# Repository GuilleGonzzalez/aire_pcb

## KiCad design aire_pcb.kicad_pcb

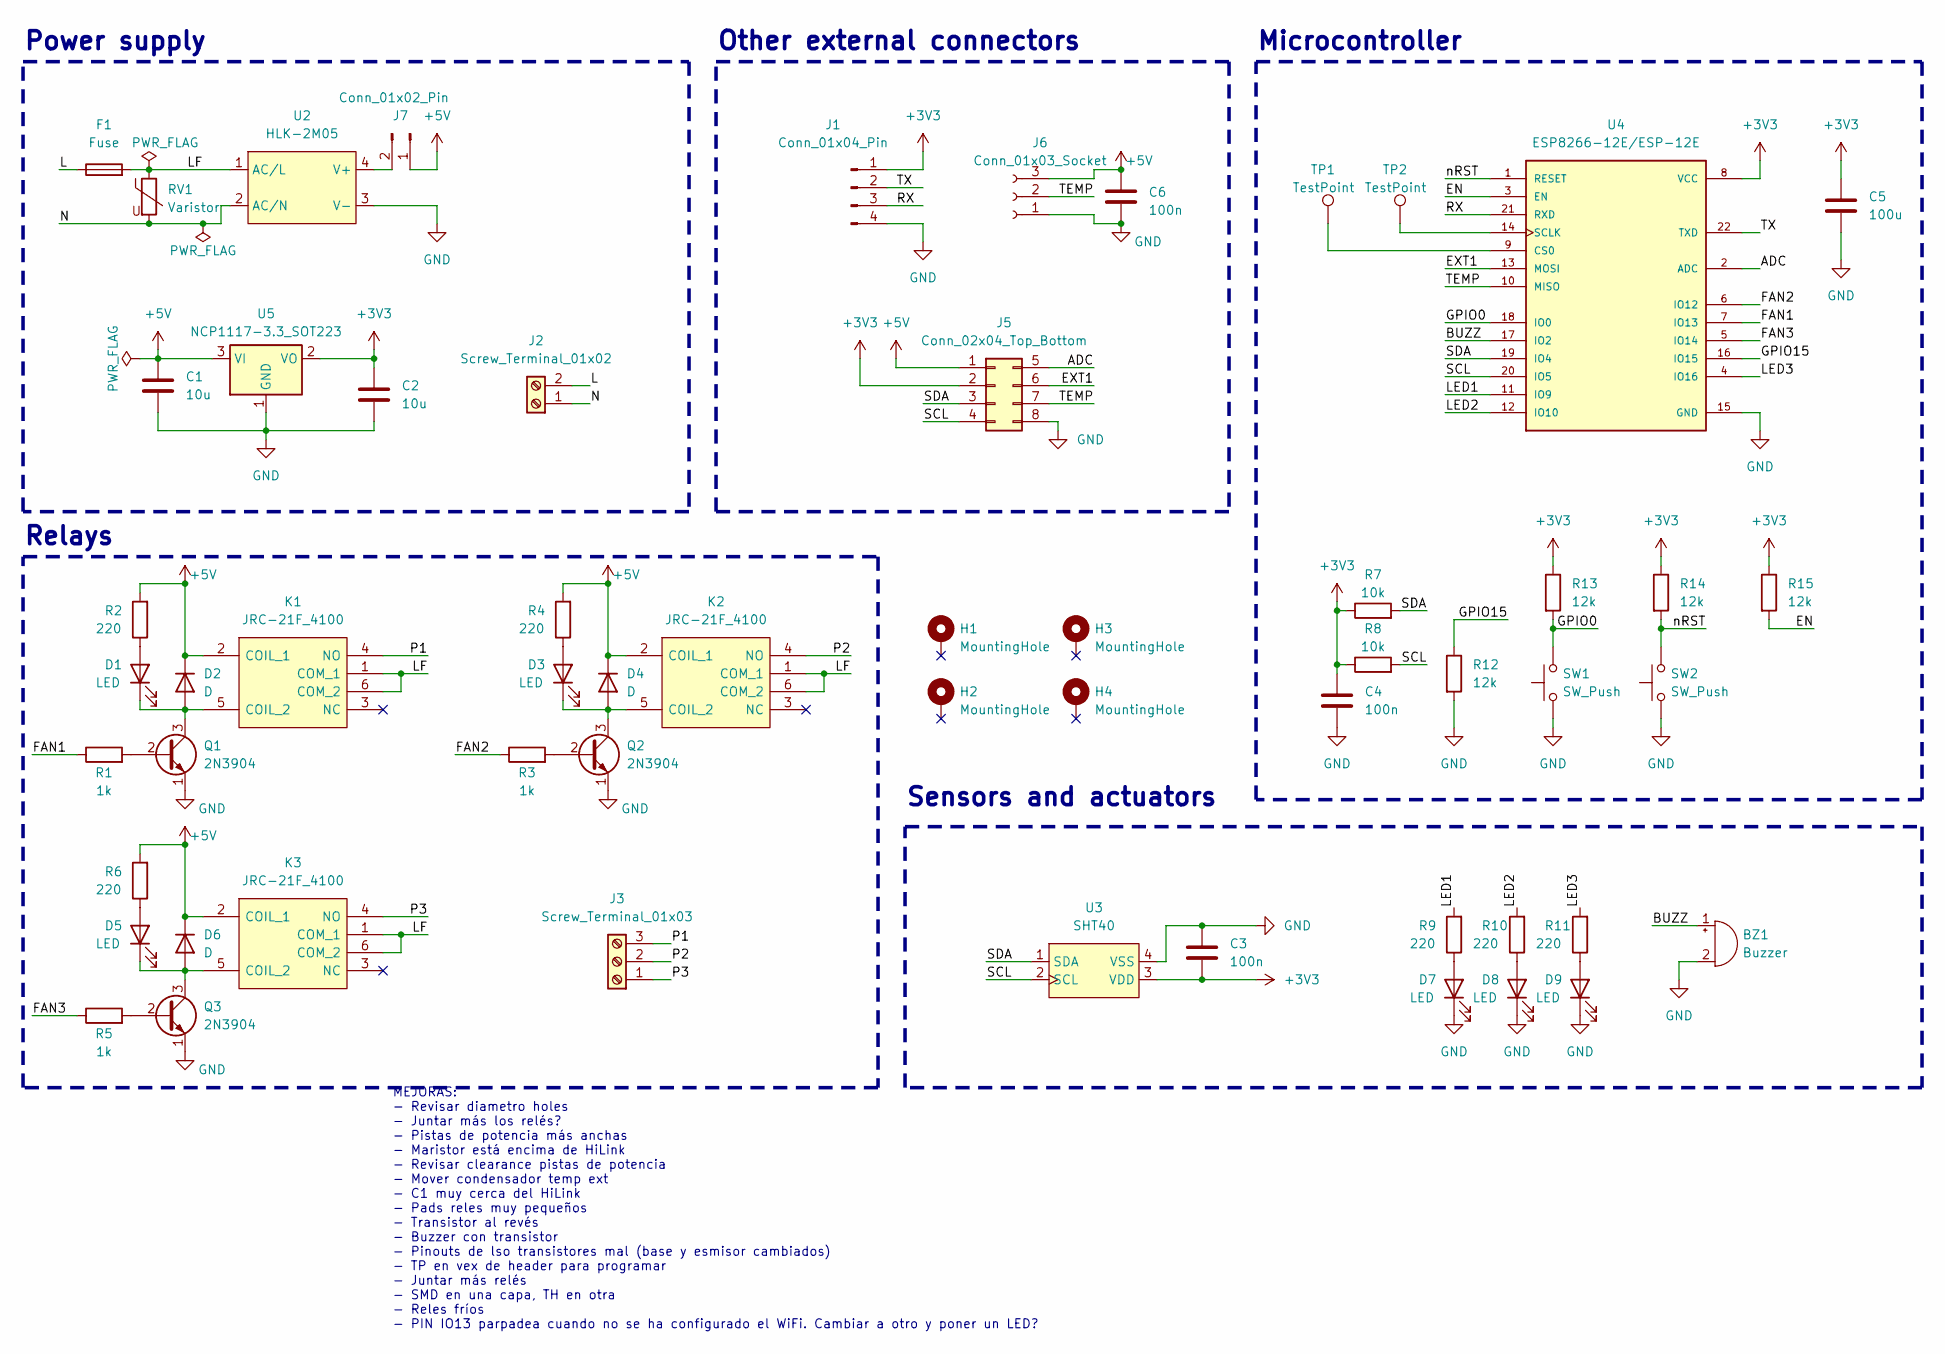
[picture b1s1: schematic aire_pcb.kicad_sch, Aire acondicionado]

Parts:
BZ1: Buzzer; Buzzer_12x9.5RM7.6
C1, C2: 10u; C_1206_3216Metric
C3, C4, C6: 100n; C_0402_1005Metric
C5: 100u; C_1206_3216Metric
D1, D3, D5: LED; LED_0402_1005Metric
D2, D4, D6: D; D_SOD-323
D7, D8, D9: LED; LED_D3.0mm
F1: Fuse; Fuse_2512_6332Metric
H1, H2, H3, H4: MountingHole; MountingHole_3.2mm_M3_Pad_TopBottom
J1: Conn_01x04_Pin; PinHeader_1x04_P2.54mm_Vertical
J2: Screw_Terminal_01x02; TerminalBlock_Phoenix_MKDS-1,5-2-5.08_1x02_P5.08mm_Horizont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
J3: Screw_Terminal_01x03; TerminalBlock_Phoenix_MKDS-1,5-3-5.08_1x03_P5.08mm_Horizont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
J5: Conn_02x04_Top_Bottom; PinHeader_2x04_P2.54mm_Vertical
J6: Conn_01x03_Socket; PinSocket_1x03_P2.54mm_Vertical
J7: Conn_01x02_Pin; PinHeader_1x02_P2.54mm_Vertical
K1, K2, K3: JRC-21F_4100; JRC21F4100; Manufacturer_Part_Number JRC-21F(4100)
Q1, Q2, Q3: 2N3904; SOT-23
R1, R3, R5: 1k; R_0402_1005Metric
R2, R4, R6, R9, R10, R11: 220; R_0402_1005Metric
R7, R8: 10k; R_0402_1005Metric
R12, R13, R14, R15: 12k; R_0402_1005Metric
RV1: Varistor; RV_Disc_D12mm_W3.9mm_P7.5mm
SW1, SW2: SW_Push; SW_SPST_PTS810
TP1, TP2: TestPoint; TestPoint_Pad_D1.5mm
U2: HLK-2M05
U3: SHT40
U4: ESP8266-12E/ESP-12E; ESP8266-12E
U5: NCP1117-3.3_SOT223; SOT-223-3_TabPin2

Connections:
+3V3: C2.1, C3.2, C4.1, C5.1, J1.1, J5.2, R7.1, R8.1, R13.1, R14.1, R15.1, U3.3 (VDD), U4.8 (VCC), U5.2 (VO)
+5V: C1.1, C6.1, D2.1 (K), D4.1 (K), D6.1 (K), J5.1, J6.3, J7.1, K1.2 (COIL_1), K2.2 (COIL_1), K3.2 (COIL_1), R2.2, R4.2, R6.2, U5.3 (VI)
/ADC: J5.5, U4.2 (ADC)
/BUZZ: BZ1.1 (-), U4.17 (IO2)
/EN: R15.2, U4.3 (EN)
/EXT1: J5.6, U4.13 (MOSI)
/FAN1: R1.1, U4.7 (IO13)
/FAN2: R3.1, U4.6 (IO12)
/FAN3: R5.1, U4.5 (IO14)
/GPIO0: R13.2, SW1.2, U4.18 (IO0)
/GPIO15: R12.1, U4.16 (IO15)
/L: F1.1, J2.2
/LED1: R9.2, U4.11 (IO9)
/LED2: R10.2, U4.12 (IO10)
/LED3: R11.2, U4.4 (IO16)
/LF: F1.2, K1.1 (COM_1), K1.6 (COM_2), K2.1 (COM_1), K2.6 (COM_2), K3.1 (COM_1), K3.6 (COM_2), RV1.1, U2.1 (AC/L)
/N: J2.1, RV1.2, U2.2 (AC/N)
/P1: J3.3, K1.4 (NO)
/P2: J3.2, K2.4 (NO)
/P3: J3.1, K3.4 (NO)
/RX: J1.3, U4.21 (RXD)
/SCL: J5.4, R8.2, U3.2 (SCL), U4.20 (IO5)
/SDA: J5.3, R7.2, U3.1 (SDA), U4.19 (IO4)
/TEMP: J5.7, J6.2, U4.10 (MISO)
/TX: J1.2, U4.22 (TXD)
/nRST: R14.2, SW2.2, U4.1 (RESET)
GND: BZ1.2 (+), C1.2, C2.2, C3.1, C4.2, C5.2, C6.2, D7.1 (K), D8.1 (K), D9.1 (K), J1.4, J5.8, J6.1, Q1.1 (E), Q2.1 (E), Q3.1 (E), R12.2, SW1.1, SW2.1, U2.3 (V-), U3.4 (VSS), U4.15 (GND), U5.1 (GND)
unnamed: D1.2 (A), R2.1
unnamed: D1.1 (K), D2.2 (A), K1.5 (COIL_2), Q1.3 (C)
unnamed: D3.2 (A), R4.1
unnamed: D3.1 (K), D4.2 (A), K2.5 (COIL_2), Q2.3 (C)
unnamed: D5.2 (A), R6.1
unnamed: D5.1 (K), D6.2 (A), K3.5 (COIL_2), Q3.3 (C)
unnamed: D7.2 (A), R9.1
unnamed: D8.2 (A), R10.1
unnamed: D9.2 (A), R11.1
unnamed: J7.2, U2.4 (V+)
unnamed: Q1.2 (B), R1.2
unnamed: Q2.2 (B), R3.2
unnamed: Q3.2 (B), R5.2
unnamed: TP1.1, U4.9 (CS0)
unnamed: TP2.1, U4.14 (SCLK)

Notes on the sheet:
Power supply
Relays
MEJORAS: - Revisar diametro holes - Juntar más los relés? - Pistas de potencia más anchas - Maristor está encima de HiLink - Revisar clearance pistas de potencia - Mover condensador temp ext - C1 muy cerca del HiLink - Pads reles muy pequeños - Transistor al revés - Buzzer con transistor - Pinouts 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
Sensors and actuators
Other external connectors
Microcontroller

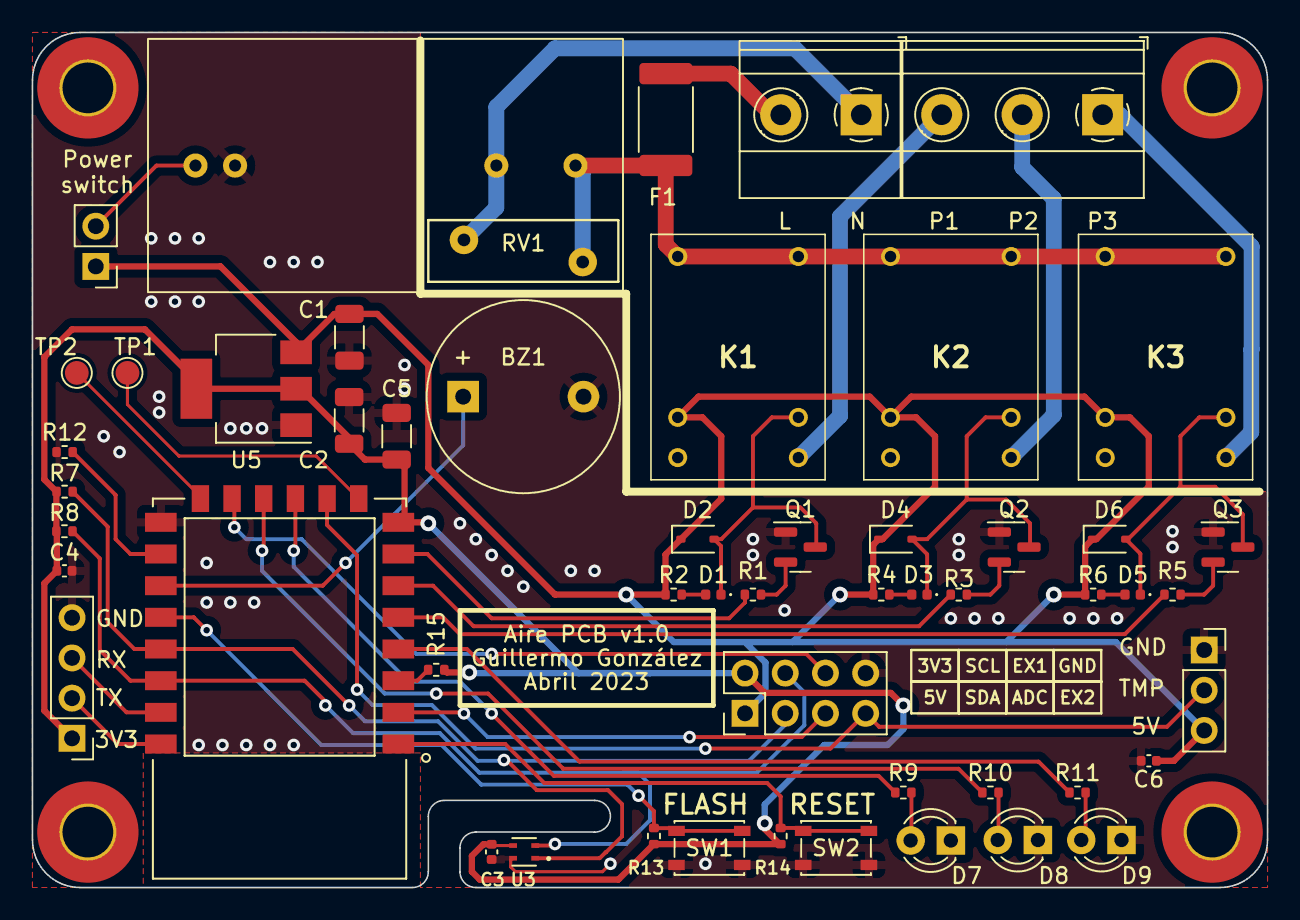
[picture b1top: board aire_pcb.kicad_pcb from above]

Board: 2 copper layers, 78.0 x 54.0 mm, 57 parts (0 on the bottom side), 42 nets.

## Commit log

2022-08-31 Add guille and esp8266 ibraries
2022-08-31 Add power and esp8266 basics to sch
2022-09-26 First sch version. Add all footprints and 3d models
2022-09-26 First placement
2022-09-26 Improve placement and add expansion conenctor
2022-09-26 Add serigraphy
2022-09-26 Route PCB with DRC ok
2022-10-06 Change transistors and diodes to SMD
2022-10-07 Change mains tracks width and improve serigraphy
2023-04-29 Minor redesign
2023-07-24 PCB changes
2023-08-29 Add GIT library
